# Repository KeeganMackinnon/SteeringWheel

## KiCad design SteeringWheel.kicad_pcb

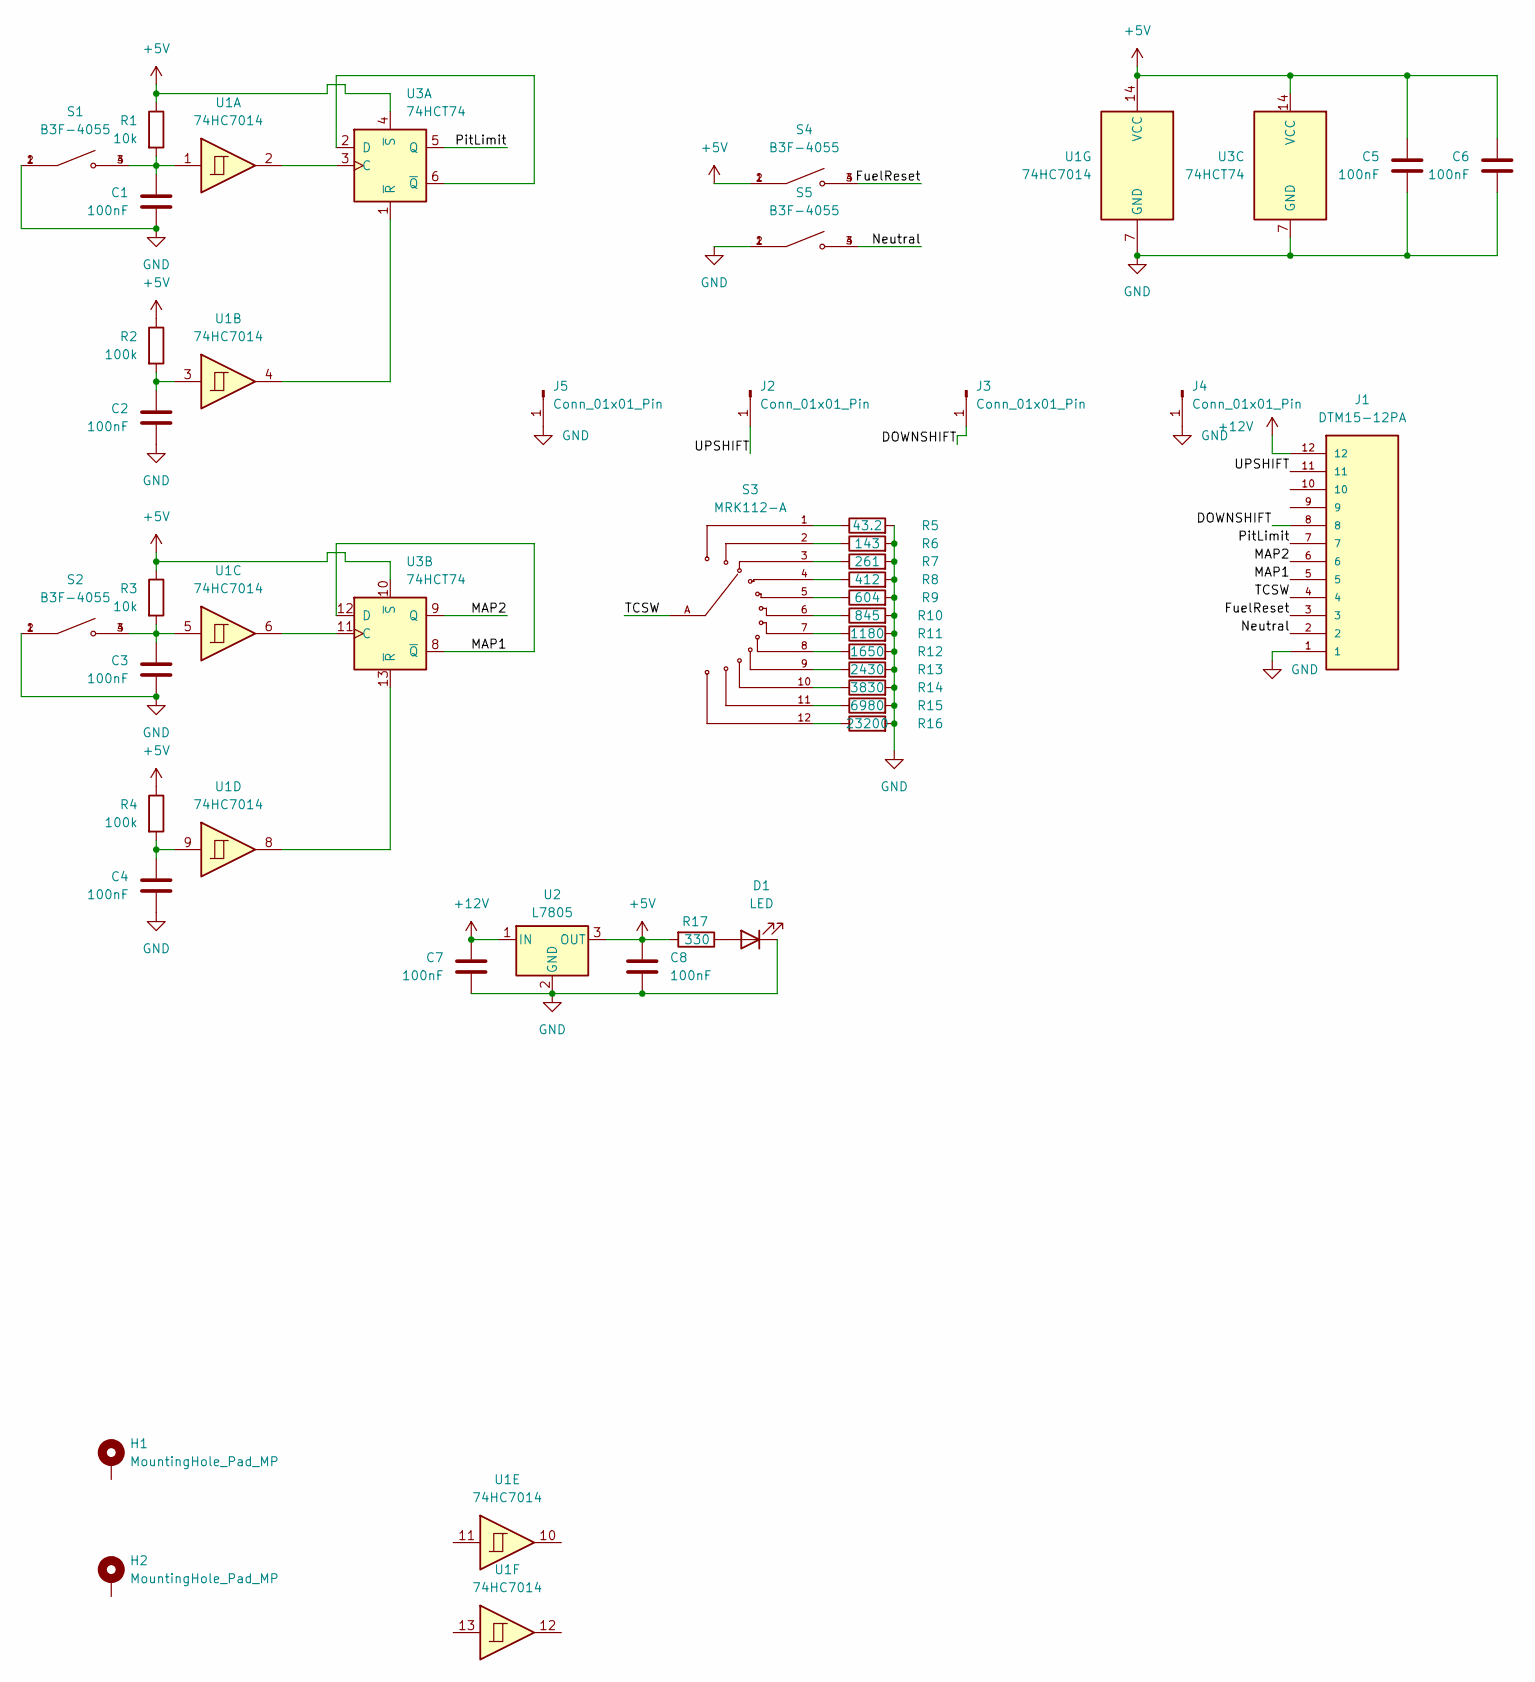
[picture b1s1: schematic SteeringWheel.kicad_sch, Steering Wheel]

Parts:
C1: 100nF; C_Axial_L3.8mm_D2.6mm_P7.50mm_Horizontal; Digikey Part Number BC2665CT-ND
C2, C3, C4, C5, C6, C7, C8: 100nF; C_Axial_L3.8mm_D2.6mm_P7.50mm_Horizontal
D1: LED; LED_D3.0mm
H1, H2: MountingHole_Pad_MP; MountingHole_3.2mm_M3_DIN965_Pad
J1: DTM15-12PA; TE_DTM15-12PA; MPN DTM15-12PA; Digikey Part Number 1734-1084-ND
J2, J3, J4, J5: Conn_01x01_Pin; SolderWire-0.25sqmm_1x01_D0.65mm_OD2mm_Relief
R1, R3: 10k; R_Axial_DIN0207_L6.3mm_D2.5mm_P10.16mm_Horizontal
R2, R4: 100k; R_Axial_DIN0207_L6.3mm_D2.5mm_P10.16mm_Horizontal
R5: 43.2; R_Axial_DIN0207_L6.3mm_D2.5mm_P10.16mm_Horizontal
R6: 143; R_Axial_DIN0207_L6.3mm_D2.5mm_P10.16mm_Horizontal
R7: 261; R_Axial_DIN0207_L6.3mm_D2.5mm_P10.16mm_Horizontal
R8: 412; R_Axial_DIN0207_L6.3mm_D2.5mm_P10.16mm_Horizontal
R9: 604; R_Axial_DIN0207_L6.3mm_D2.5mm_P10.16mm_Horizontal
R10: 845; R_Axial_DIN0207_L6.3mm_D2.5mm_P10.16mm_Horizontal
R11: 1180; R_Axial_DIN0207_L6.3mm_D2.5mm_P10.16mm_Horizontal
R12: 1650; R_Axial_DIN0207_L6.3mm_D2.5mm_P10.16mm_Horizontal
R13: 2430; R_Axial_DIN0207_L6.3mm_D2.5mm_P10.16mm_Horizontal
R14: 3830; R_Axial_DIN0207_L6.3mm_D2.5mm_P10.16mm_Horizontal
R15: 6980; R_Axial_DIN0207_L6.3mm_D2.5mm_P10.16mm_Horizontal
R16: 23200; R_Axial_DIN0207_L6.3mm_D2.5mm_P10.16mm_Horizontal
R17: 330; R_Axial_DIN0207_L6.3mm_D2.5mm_P10.16mm_Horizontal
S1, S2, S4, S5: B3F-4055; SW_B3F-4055; PARTREV A070-E1-08; Digikey Part Number SW414-ND
S3: MRK112-A; SW_MRK112-A; PARTREV N/A; Digikey Part Number 360-2372-ND
U1: 74HC7014; DIP-14_W7.62mm; Digikey Part Number 296-12786-5-ND
U2: L7805; TO-220-3_Horizontal_TabDown
U3: 74HCT74; DIP-14_W7.62mm; Digikey Part Number 296-2132-5-ND

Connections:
+5V: C5.1, C6.1, C8.1, R1.1, R2.1, R3.1, R4.1, R17.2, S4.1, S4.2, U1.14 (VCC), U2.3 (OUT), U3.4 (~S), U3.10 (~S), U3.14 (VCC)
+12V: C7.1, J1.12, U2.1 (IN)
/DOWNSHIFT: J1.8, J3.1
/FuelReset: J1.3, S4.3, S4.4
/MAP1: J1.5, U3.8 (~Q), U3.12 (D)
/MAP2: J1.6, U3.9 (Q)
/Neutral: J1.2, S5.3, S5.4
/PitLimit: J1.7, U3.5 (Q)
/TCSW: J1.4, S3.A
/UPSHIFT: J1.11, J2.1
GND: C1.2, C2.2, C3.2, C4.2, C5.2, C6.2, C7.2, C8.2, D1.1 (K), J1.1, J4.1, J5.1, R5.2, R6.2, R7.2, R8.2, R9.2, R10.2, R11.2, R12.2, R13.2, R14.2, R15.2, R16.2, S1.1, S1.2, S2.1, S2.2, S5.1, S5.2, U1.7 (GND), U2.2 (GND), U3.7 (GND)
unnamed: C1.1, R1.2, S1.3, S1.4, U1.1
unnamed: C2.1, R2.2, U1.3
unnamed: C3.1, R3.2, S2.3, S2.4, U1.5
unnamed: C4.1, R4.2, U1.9
unnamed: D1.2 (A), R17.1
unnamed: R5.1, S3.1
unnamed: R6.1, S3.2
unnamed: R7.1, S3.3
unnamed: R8.1, S3.4
unnamed: R9.1, S3.5
unnamed: R10.1, S3.6
unnamed: R11.1, S3.7
unnamed: R12.1, S3.8
unnamed: R13.1, S3.9
unnamed: R14.1, S3.10
unnamed: R15.1, S3.11
unnamed: R16.1, S3.12
unnamed: U1.2, U3.3 (C)
unnamed: U3.2 (D), U3.6 (~Q)
unnamed: U1.4, U3.1 (~R)
unnamed: U1.6, U3.11 (C)
unnamed: U1.8, U3.13 (~R)

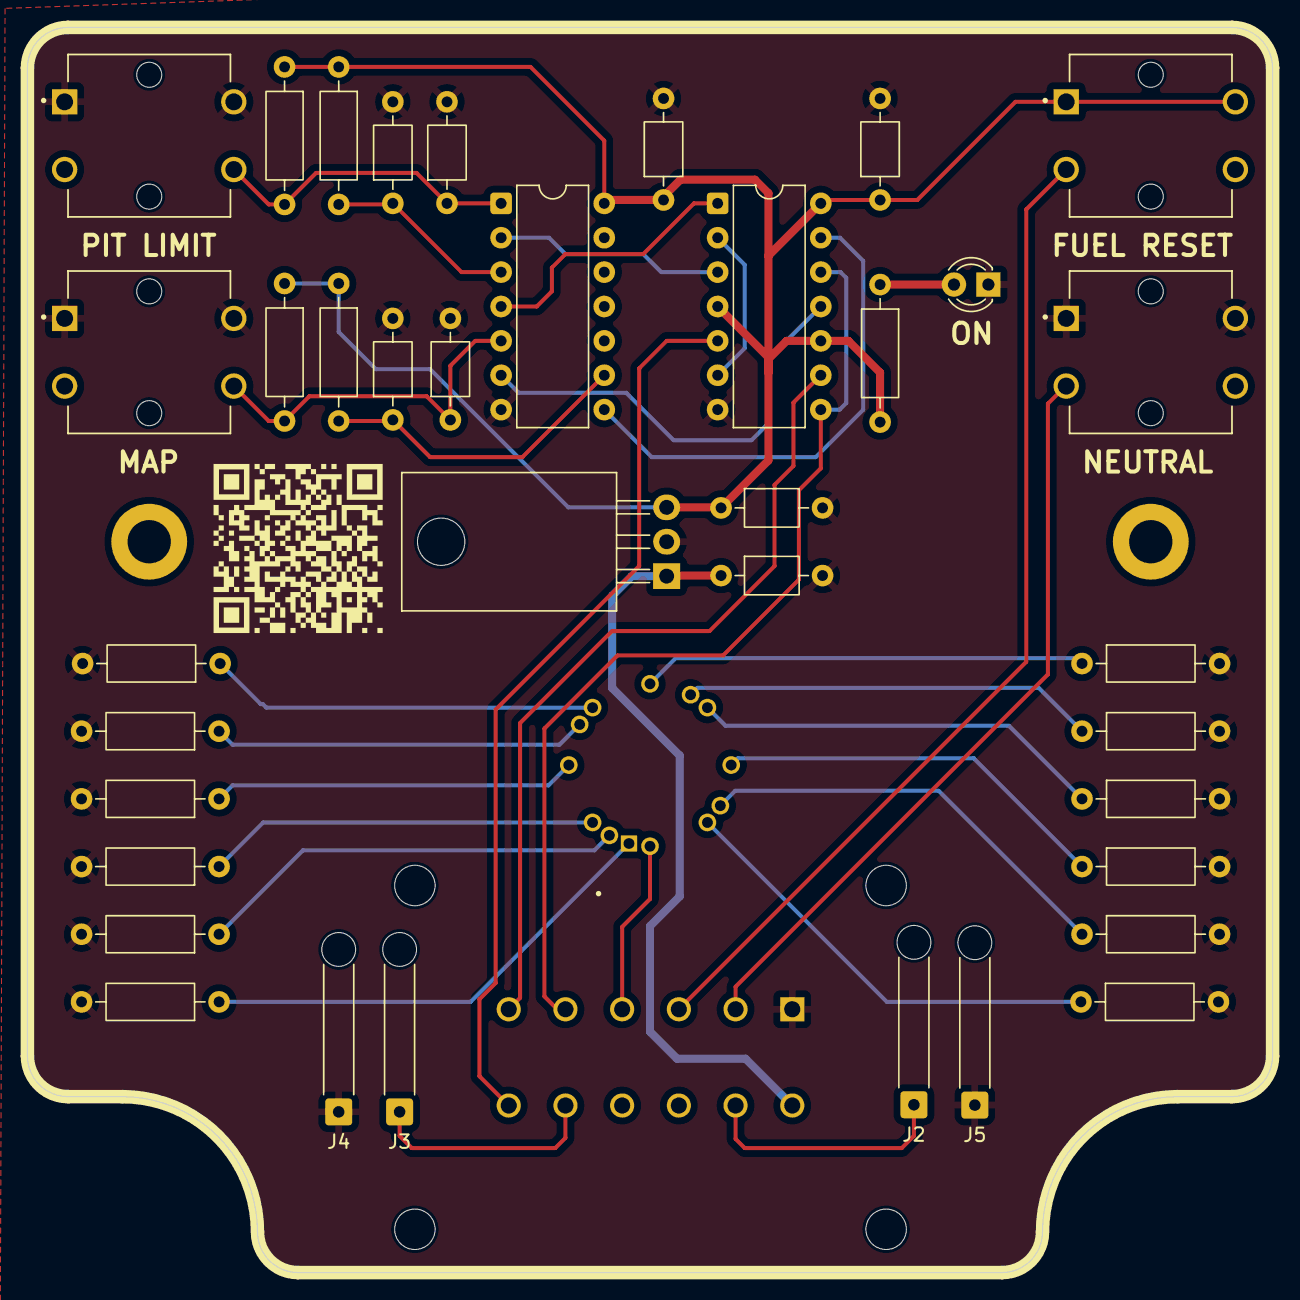
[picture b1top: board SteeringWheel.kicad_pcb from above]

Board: 2 copper layers, 92.0 x 92.0 mm, 41 parts (1 on the bottom side), 33 nets.

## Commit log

2026-02-05 Component Placement Finished
2026-03-05 Rev 1 Prod
